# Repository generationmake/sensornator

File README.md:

# Sensornator
Board with ESP32 in the Arduino Uno form factor

## PCB

### Top

### Bottom

## License

This hardware is licensed under the CERN OHL v. 1.2

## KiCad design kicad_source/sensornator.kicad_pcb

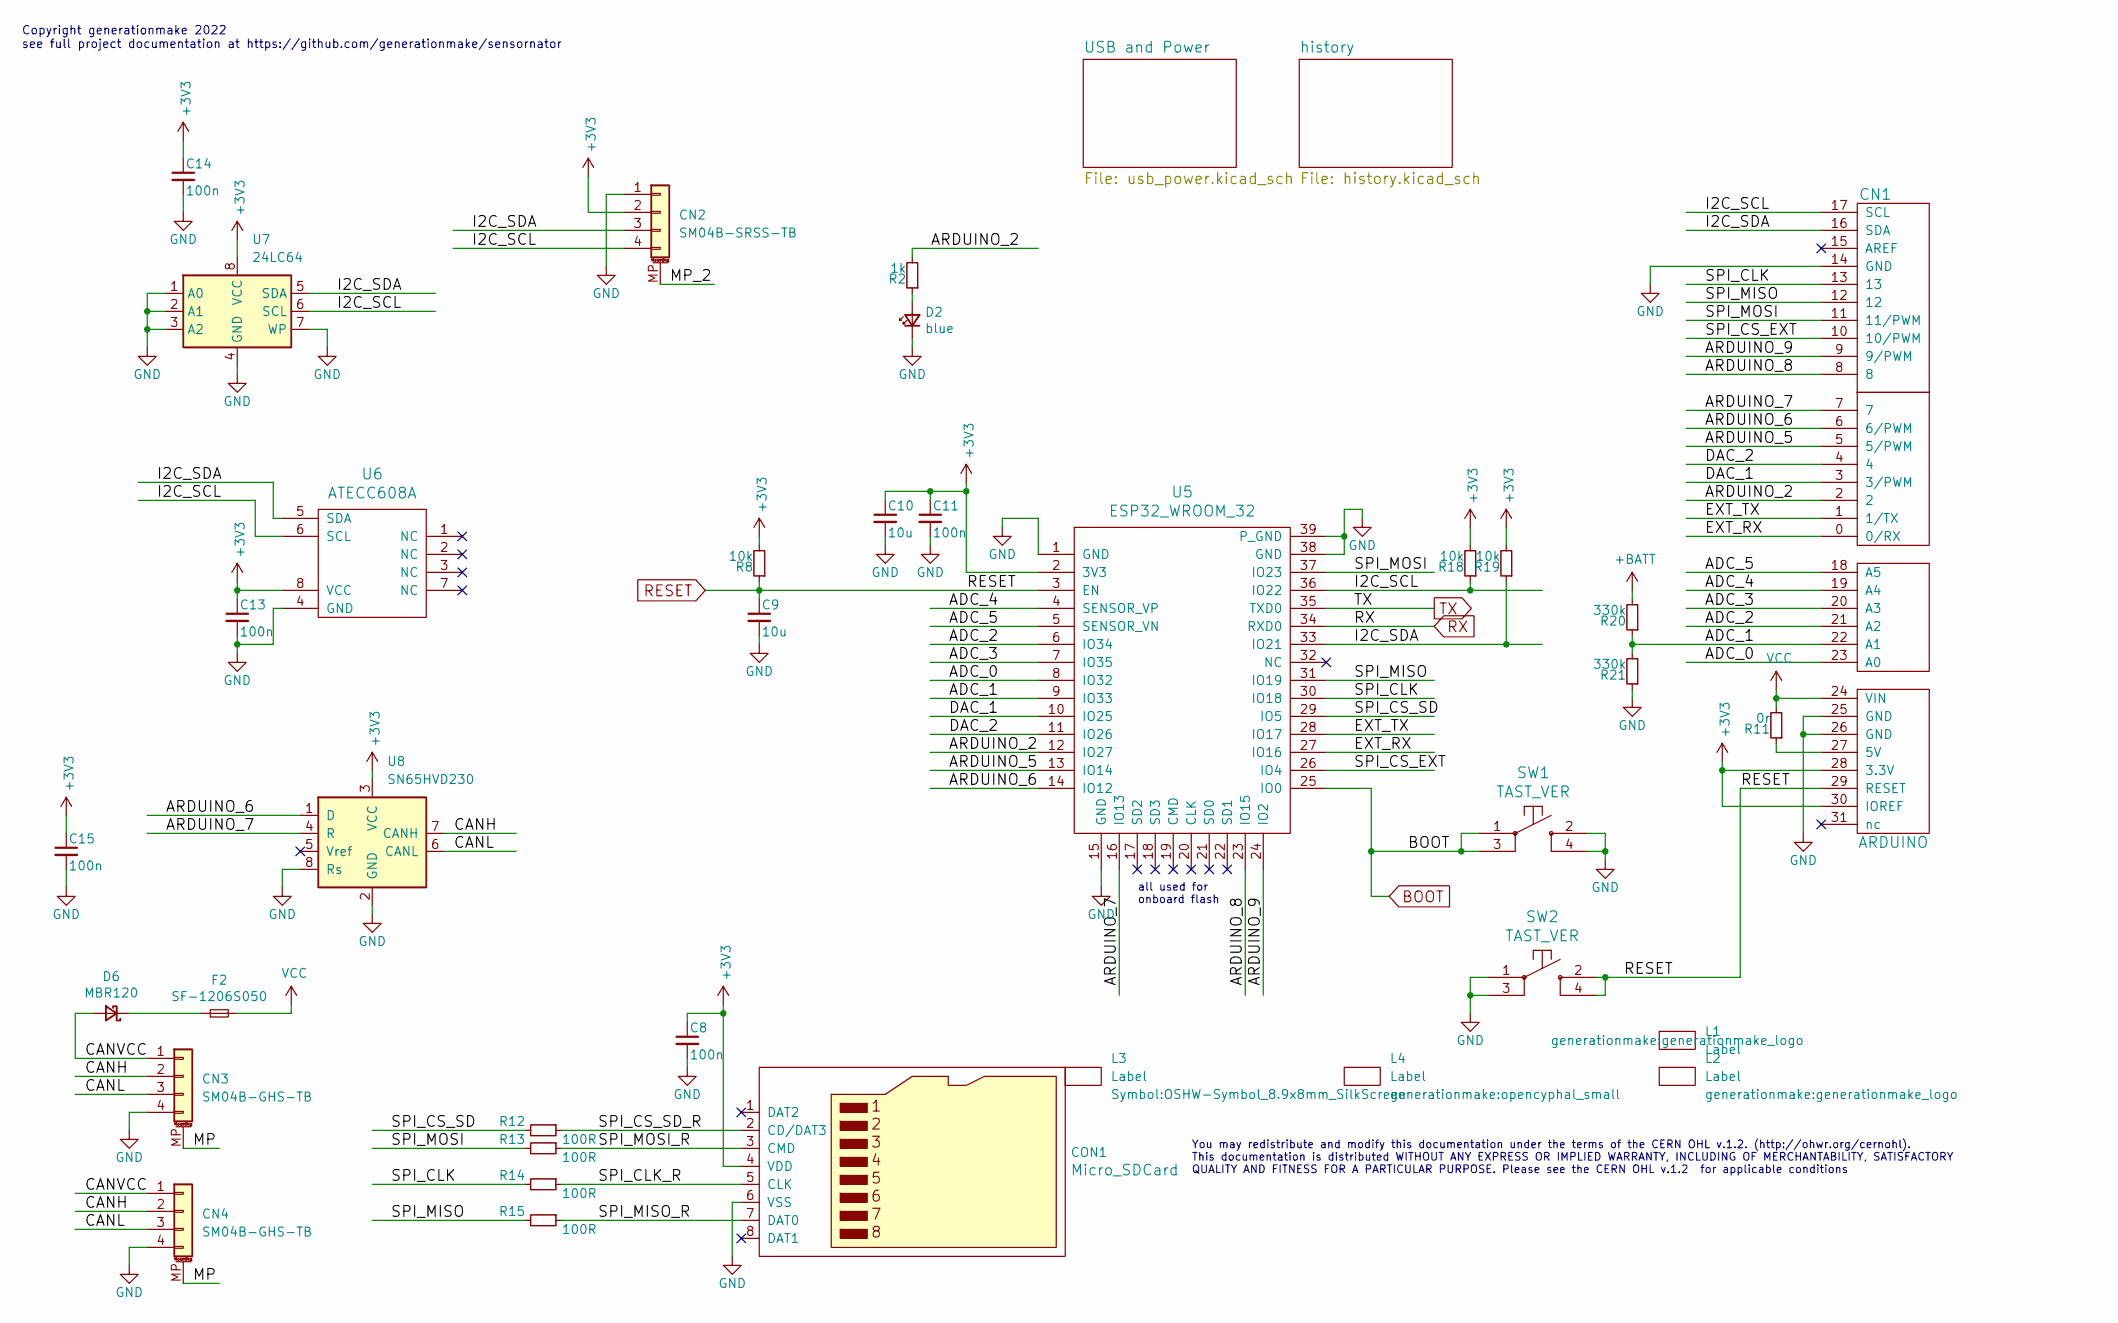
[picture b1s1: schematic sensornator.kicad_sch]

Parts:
C8, C11, C13, C14, C15: 100n; C_0603_1608Metric
C9, C10: 10u; C_0603_1608Metric
CN1: ARDUINO
CN2: SM04B-SRSS-TB; JST_SH_SM04B-SRSS-TB_1x04-1MP_P1.00mm_Horizontal
CN3, CN4: SM04B-GHS-TB; JST_GH_SM04B-GHS-TB_1x04-1MP_P1.25mm_Horizontal
CON1: Micro_SDCard; WE_693071010811
D2: blue; LED_0603_1608Metric
D6: MBR120; D_SOD-123
F2: SF-1206S050; Fuse_1206_3216Metric
L1, L2: Label; generationmake_logo
L3: Label; OSHW-Symbol_8.9x8mm_SilkScreen
L4: Label; opencyphal_small
R2: 1k; R_0603_1608Metric
R8, R18, R19: 10k; R_0603_1608Metric
R11: 0r; R_0603_1608Metric
R12, R13, R14, R15: 100R; R_0603_1608Metric
R20, R21: 330k; R_0603_1608Metric
SW1, SW2: TAST_VER; WE_430182050816
U5: ESP32_WROOM_32; ESP32-WROOM-32
U6: ATECC608A; SOIC-8_3.9x4.9mm_P1.27mm
U7: 24LC64; SOIC-8_3.9x4.9mm_P1.27mm
U8: SN65HVD230; SOIC-8_3.9x4.9mm_P1.27mm

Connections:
+3V3: C8.1, C10.1, C11.1, C13.1, C14.1, C15.1, CN1.28 (3.3V), CN1.30 (IOREF), CN2.2, CON1.4 (VDD), R8.2, R18.2, R19.2, U5.2 (3V3), U6.8 (VCC), U7.8 (VCC), U8.3 (VCC); also elsewhere on the board
+BATT: R20.2; also elsewhere on the board
/ADC_0: CN1.23 (A0), U5.8 (IO32)
/ADC_1: CN1.22 (A1), R20.1, R21.2, U5.9 (IO33)
/ADC_2: CN1.21 (A2), U5.6 (IO34)
/ADC_3: CN1.20 (A3), U5.7 (IO35)
/ADC_4: CN1.19 (A4), U5.4 (SENSOR_VP)
/ADC_5: CN1.18 (A5), U5.5 (SENSOR_VN)
/ARDUINO_2: CN1.2, R2.2, U5.12 (IO27)
/ARDUINO_5: CN1.5 (5/PWM), U5.13 (IO14)
/ARDUINO_6: CN1.6 (6/PWM), U5.14 (IO12), U8.1 (D)
/ARDUINO_7: CN1.7, U5.16 (IO13), U8.4 (R)
/ARDUINO_8: CN1.8, U5.23 (IO15)
/ARDUINO_9: CN1.9 (9/PWM), U5.24 (IO2)
/CANH: CN3.2, CN4.2, U8.7 (CANH)
/CANL: CN3.3, CN4.3, U8.6 (CANL)
/CANVCC: CN3.1, CN4.1, D6.2 (A)
/DAC_1: CN1.3 (3/PWM), U5.10 (IO25)
/DAC_2: CN1.4, U5.11 (IO26)
/EXT_RX: CN1.0 (0/RX), U5.27 (IO16)
/EXT_TX: CN1.1 (1/TX), U5.28 (IO17)
/I2C_SCL: CN1.17 (SCL), CN2.4, R18.1, U5.36 (IO22), U6.6 (SCL), U7.6 (SCL)
/I2C_SDA: CN1.16 (SDA), CN2.3, R19.1, U5.33 (IO21), U6.5 (SDA), U7.5 (SDA)
/MP: CN3.MP (MountPin), CN4.MP (MountPin)
/MP_2: CN2.MP (MountPin)
/SPI_CLK: CN1.13, R14.2, U5.30 (IO18)
/SPI_CLK_R: CON1.5 (CLK), R14.1
/SPI_CS_EXT: CN1.10 (10/PWM), U5.26 (IO4)
/SPI_CS_SD: R12.2, U5.29 (IO5)
/SPI_CS_SD_R: CON1.2 (CD/DAT3), R12.1
/SPI_MISO: CN1.12, R15.2, U5.31 (IO19)
/SPI_MISO_R: CON1.7 (DAT0), R15.1
/SPI_MOSI: CN1.11 (11/PWM), R13.2, U5.37 (IO23)
/SPI_MOSI_R: CON1.3 (CMD), R13.1
BOOT: SW1.1, SW1.3, U5.25 (IO0); also elsewhere on the board
GND: C8.2, C9.2, C10.2, C11.2, C13.2, C14.2, C15.2, CN1.14 (GND), CN1.25 (GND), CN1.26 (GND), CN2.1, CN3.4, CN4.4, CON1.6 (VSS), D2.1 (K), R21.1, SW1.2, SW1.4, SW2.1, SW2.3, U5.1 (GND), U5.15 (GND), U5.38 (GND), U5.39 (P_GND), U6.4 (GND), U7.1 (A0), U7.2 (A1), U7.3 (A2), U7.4 (GND), U7.7 (WP), U8.2 (GND), U8.8 (Rs); also elsewhere on the board
unnamed: CN1.27 (5V), R11.1
unnamed: D2.2 (A), R2.1
unnamed: D6.1 (K), F2.1
RESET: C9.1, CN1.29 (RESET), R8.1, SW2.2, SW2.4, U5.3 (EN); also elsewhere on the board
RX: U5.34 (RXD0); also elsewhere on the board
TX: U5.35 (TXD0); also elsewhere on the board
VCC: CN1.24 (VIN), F2.2, R11.2; also elsewhere on the board

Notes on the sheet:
Copyright generationmake 2022 see full project documentation at https://github.com/generationmake/sensornator
all used for onboard flash
You may redistribute and modify this documentation under the terms of the CERN OHL v.1.2. (http://ohwr.org/cernohl). This documentation is distributed WITHOUT ANY EXPRESS OR IMPLIED WARRANTY, INCLUDING OF MERCHANTABILITY, SATISFACTORY QUALITY AND FITNESS FOR A PARTICULAR PURPOSE. Please see the CER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

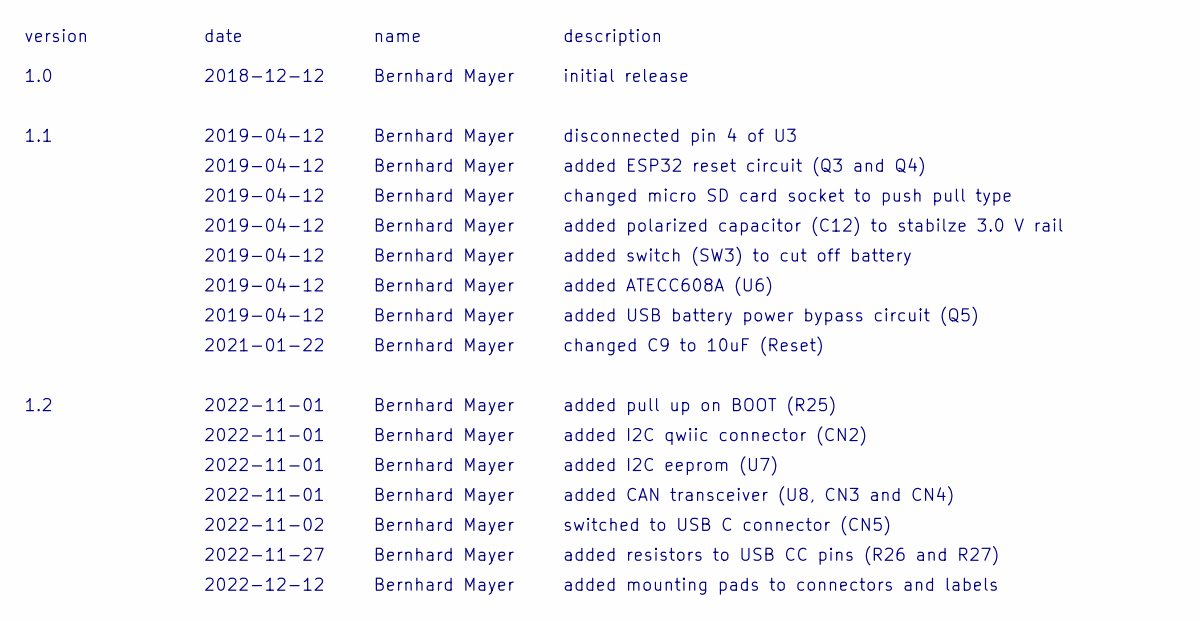
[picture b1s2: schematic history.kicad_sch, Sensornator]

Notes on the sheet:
added ESP32 reset circuit (Q3 and Q4)
added CAN transceiver (U8, CN3 and CN4)
Bernhard Mayer
added ATECC608A (U6)
initial release
2019-04-12
2021-01-22
2022-11-01
switched to USB C connector (CN5)
date
added I2C eeprom (U7)
added polarized capacitor (C12) to stabilze 3.0 V rail
version
name
description
changed micro SD card socket to push pull type
added pull up on BOOT (R25)
2022-11-27
2022-12-12
1.1
added USB battery power bypass circuit (Q5)
2022-11-02
added mounting pads to connectors and labels
added resistors to USB CC pins (R26 and R27)
disconnected pin 4 of U3
added switch (SW3) to cut off battery
1.0
changed C9 to 10uF (Reset)
2018-12-12
added I2C qwiic connector (CN2)
1.2

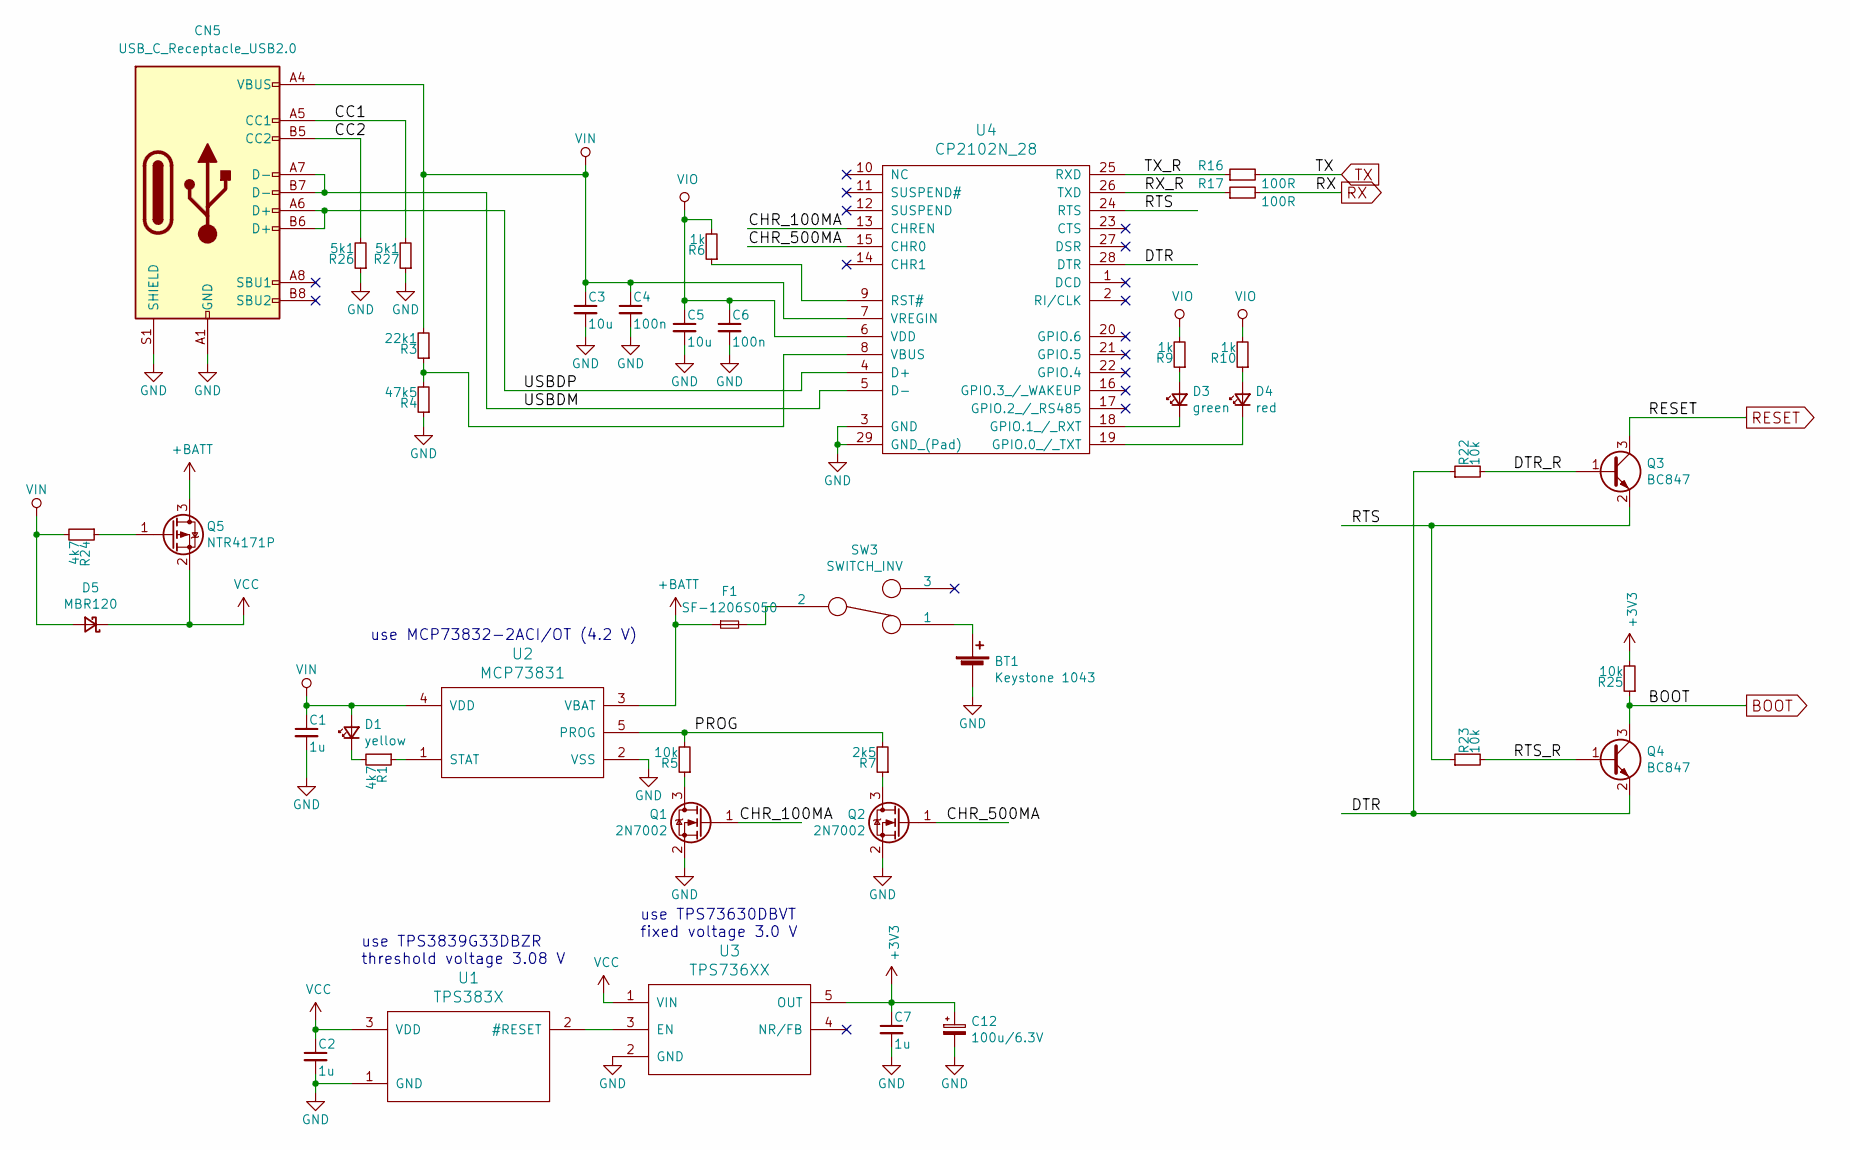
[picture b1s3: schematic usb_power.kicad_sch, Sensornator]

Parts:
BT1: Keystone 1043; KEYSTONE_1043
C1, C2, C7: 1u; C_0603_1608Metric
C3, C5: 10u; C_0603_1608Metric
C4, C6: 100n; C_0603_1608Metric
C12: 100u/6.3V; CP_EIA-7343-31_Kemet-D
CN5: USB_C_Receptacle_USB2.0; USB_C_Receptacle_Amphenol_12401610E4-2A
D1: yellow; LED_0603_1608Metric
D3: green; LED_0603_1608Metric
D4: red; LED_0603_1608Metric
D5: MBR120; D_SOD-123
F1: SF-1206S050; Fuse_1206_3216Metric
Q1, Q2: 2N7002; SOT-23
Q3, Q4: BC847; SOT-23
Q5: NTR4171P; SOT-23
R1, R24: 4k7; R_0603_1608Metric
R3: 22k1; R_0603_1608Metric
R4: 47k5; R_0603_1608Metric
R5, R22, R23, R25: 10k; R_0603_1608Metric
R6, R9, R10: 1k; R_0603_1608Metric
R7: 2k5; R_0603_1608Metric
R16, R17: 100R; R_0603_1608Metric
R26, R27: 5k1; R_0603_1608Metric
SW3: SWITCH_INV; WE_450404015514
U1: TPS383X; SOT-23
U2: MCP73831; SOT-23-5
U3: TPS736XX; SOT-23-5
U4: CP2102N_28; QFN-28-1EP_5x5mm_P0.5mm_EP3.35x3.35mm

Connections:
+3V3: C7.1, C12.1, R25.2, U3.5 (OUT); also elsewhere on the board
+BATT: F1.1, Q5.3 (D), U2.3 (VBAT); also elsewhere on the board
/USB and Power/CC1: CN5.A5 (CC1), R27.2
/USB and Power/CC2: CN5.B5 (CC2), R26.2
/USB and Power/CHR_100MA: Q1.1 (G), U4.13 (CHREN)
/USB and Power/CHR_500MA: Q2.1 (G), U4.15 (CHR0)
/USB and Power/DTR: Q4.2 (E), R22.1, U4.28 (DTR)
/USB and Power/DTR_R: Q3.1 (B), R22.2
/USB and Power/PROG: R5.2, R7.2, U2.5 (PROG)
/USB and Power/RTS: Q3.2 (E), R23.1, U4.24 (RTS)
/USB and Power/RTS_R: Q4.1 (B), R23.2
/USB and Power/RX_R: R17.1, U4.26 (TXD)
/USB and Power/TX_R: R16.1, U4.25 (RXD)
/USB and Power/USBDM: CN5.A7 (D-), CN5.B7 (D-), U4.5 (D-)
/USB and Power/USBDP: CN5.A6 (D+), CN5.B6 (D+), U4.4 (D+)
BOOT: Q4.3 (C), R25.1; also elsewhere on the board
GND: BT1.2 (-), C1.2, C2.2, C3.2, C4.2, C5.2, C6.2, C7.2, C12.2, CN5.A1 (GND), CN5.A12 (GND), CN5.B1 (GND), CN5.B12 (GND), CN5.S1 (SHIELD), Q1.2 (S), Q2.2 (S), R4.1, R26.1, R27.1, U1.1 (GND), U2.2 (VSS), U3.2 (GND), U4.3 (GND), U4.29 (GND_(Pad)); also elsewhere on the board
unnamed: BT1.1 (+), SW3.1
unnamed: D1.1 (K), R1.2
unnamed: D3.1 (K), U4.18 (GPIO.1_/_RXT)
unnamed: D3.2 (A), R9.1
unnamed: D4.1 (K), U4.19 (GPIO.0_/_TXT)
unnamed: D4.2 (A), R10.1
unnamed: F1.2, SW3.2
unnamed: Q1.3 (D), R5.1
unnamed: Q2.3 (D), R7.1
unnamed: Q5.1 (G), R24.1
unnamed: R1.1, U2.1 (STAT)
unnamed: R3.1, R4.2, U4.8 (VBUS)
unnamed: R6.1, U4.9 (RST#)
unnamed: U1.2 (#RESET), U3.3 (EN)
RESET: Q3.3 (C); also elsewhere on the board
RX: R17.2; also elsewhere on the board
TX: R16.2; also elsewhere on the board
VCC: C2.1, D5.1 (K), Q5.2 (S), U1.3 (VDD), U3.1 (VIN); also elsewhere on the board
VIN: C1.1, C3.1, C4.1, CN5.A4 (VBUS), CN5.A9 (VBUS), CN5.B4 (VBUS), CN5.B9 (VBUS), D1.2 (A), D5.2 (A), R3.2, R24.2, U2.4 (VDD), U4.7 (VREGIN)
VIO: C5.1, C6.1, R6.2, R9.2, R10.2, U4.6 (VDD)

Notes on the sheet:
use MCP73832-2ACI/OT (4.2 V)
use TPS3839G33DBZR threshold voltage 3.08 V
use TPS73630DBVT fixed voltage 3.0 V

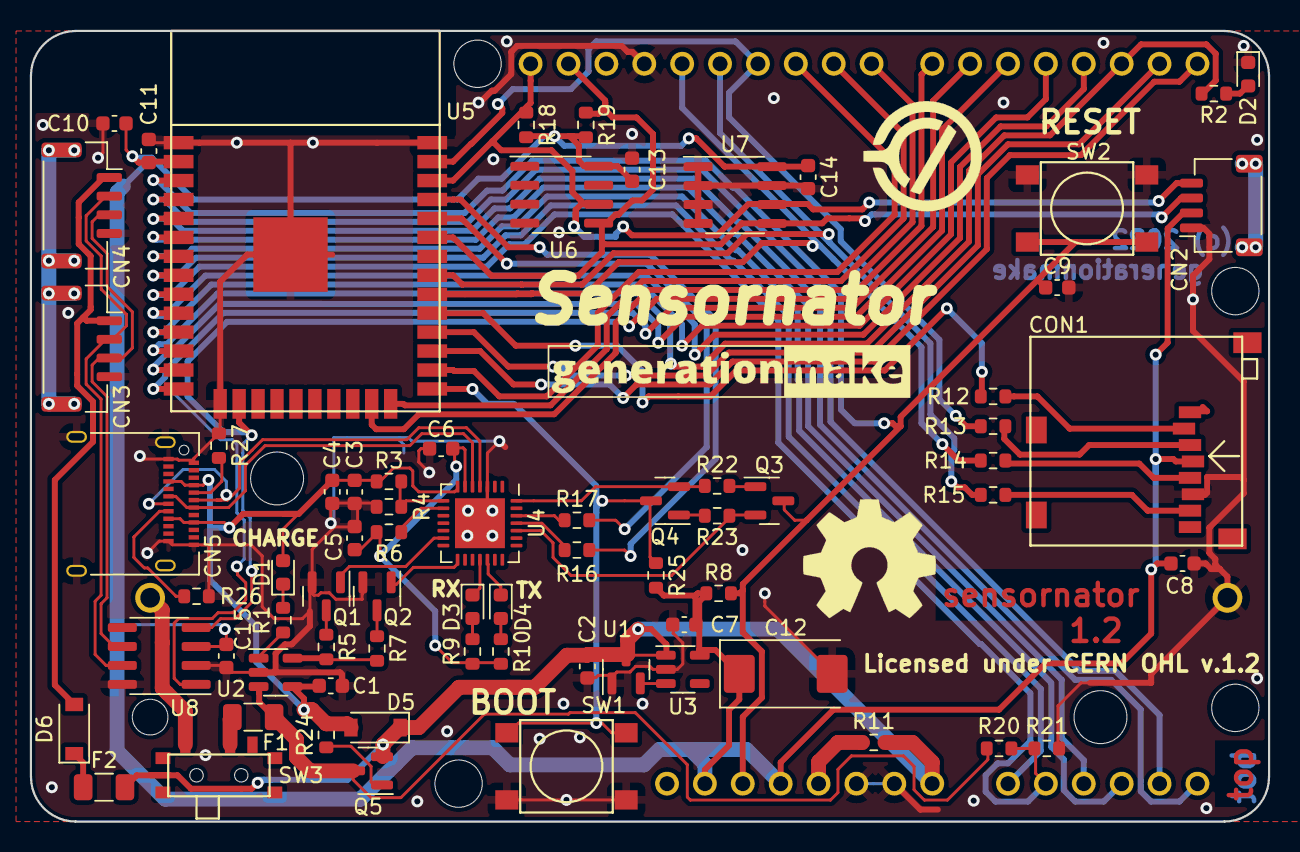
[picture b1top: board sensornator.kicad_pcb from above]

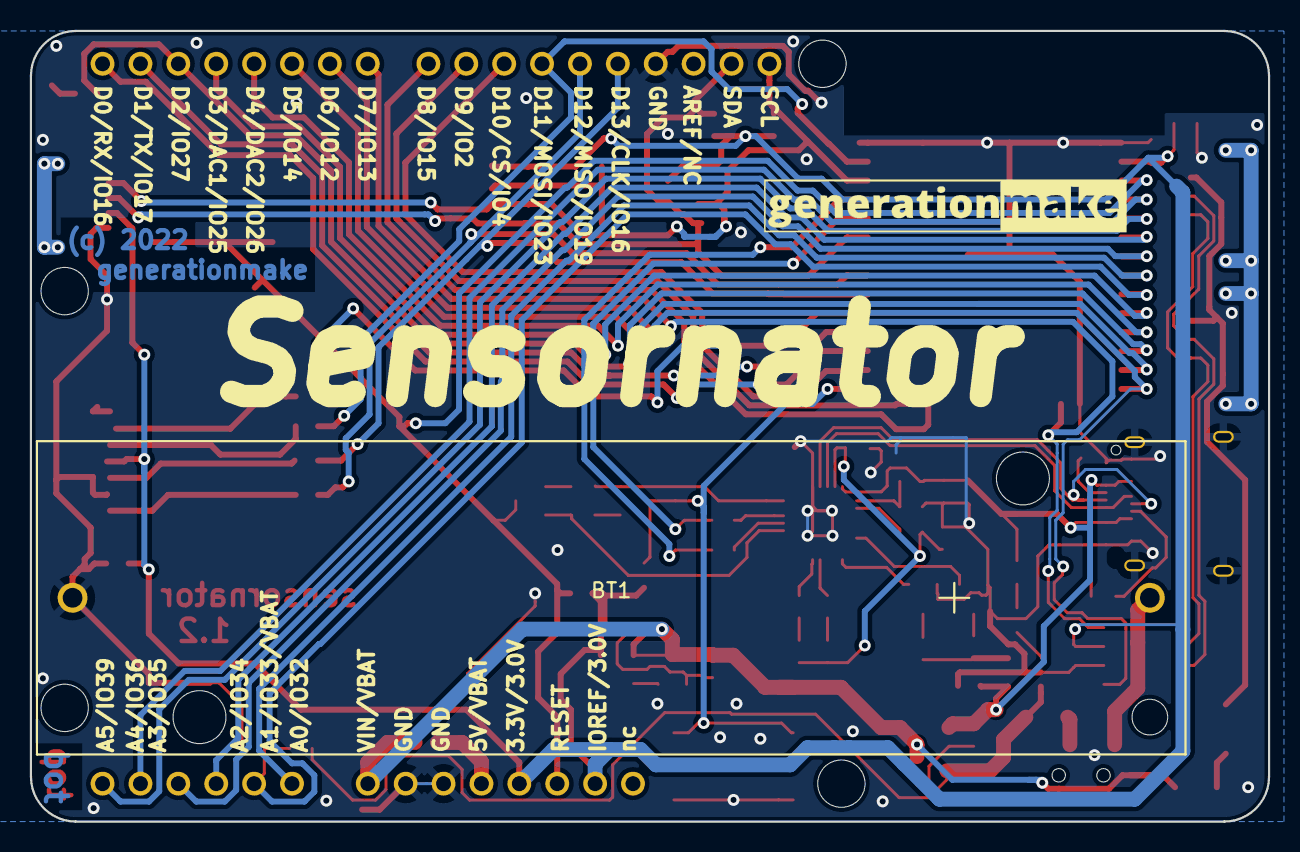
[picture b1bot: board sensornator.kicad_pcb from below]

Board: 2 copper layers, 83.0 x 53.0 mm, 77 parts (2 on the bottom side), 71 nets.

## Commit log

2018-12-04 added poject files
2018-12-04 corrected library refs
2018-12-05 started schematic added ESP32
2018-12-10 added power supply parts, first try for connection with arduino header
2018-12-10 corrected schematic, updated layout
2018-12-10 updated pdf schematic
2018-12-11 finished layout, created gerber
2019-02-07 corrected schematic and layout, generated gerber
2019-02-10 corrected schematic error at voltage regulator, added resistor values
2019-02-17 added some comments, updated some values
2019-03-19 added some values in schemtaic
2019-03-19 updated netlist and layout
2019-04-12 renamed files to sensornator
2019-04-12 renamed folder to sensornator
2019-04-12 updated schematic, added extra pages for history and usb, added esp32 reset circuit
2019-04-12 changed micro SD card socket to push pull type, updated footprint of micro USB socket
2019-04-12 updated schematic, added USB voltage bypass, finished layout, corrected 3D models
2019-04-12 added silk screen on back side, updated parameters, generated pdf schematic
2019-04-12 added some part values
2021-01-21 moved files to correct folder
2021-01-22 added readme
2021-01-22 updated to latest KiCAD version
2021-01-22 changed C9 to 10u (reset), updated schematic pdf
2021-01-22 added images
2022-11-01 update to kicad 6
2022-11-01 added pull up on BOOT
2022-11-01 added qwiic connector
2022-11-01 added i2c eeprom
2022-11-01 updated footprint libraries
2022-11-01 added CAN transceiver
2022-11-27 added usb c connector
2022-11-28 added resistors on USB CC
2022-11-28 fixedsome drc errors
2022-12-12 added mounting pins on connectors, added labels
2023-01-10 updated schematic pdf
2023-01-10 updated images

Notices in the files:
kicad_source/history.kicad_sch:
This documentation describes Open Hardware and is licensed under the CERN OHL v. 1.2.
kicad_source/sensornator.kicad_pcb:
Licensed under CERN OHL v.1.2
